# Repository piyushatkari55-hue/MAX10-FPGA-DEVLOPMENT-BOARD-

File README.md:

# MAX 10 FPGA Development Board

## Project Overview
This project focuses on designing a custom FPGA development board based on the **Intel MAX 10 10M02SC E144 (C7G)** FPGA using KiCad EDA.

The aim is to develop a compact, low-cost and beginner-friendly FPGA development platform for learning, testing, and implementing digital logic applications.

## Main Objectives
- Design a complete FPGA schematic and PCB layout.
- Implement suitable power management for the FPGA and peripherals.
- Provide a JTAG interface for FPGA programming and debugging.
- Design clock and FPGA configuration circuits.
- Expose FPGA GPIO pins through expansion headers.
- Develop a compact PCB while following FPGA layout guidelines.

## Hardware Features
- **FPGA:** Intel MAX 10 10M02SC E144
- **EDA Tool:** KiCad
- **Programming Interface:** JTAG
- **Clock Circuit:** External clock source
- **Power Management:** Voltage regulation and decoupling
- **Expansion:** GPIO headers for external peripherals

## Repository Structure
- `10M02SCE144C7G.kicad_pro` – KiCad project file
- `10M02SCE144C7G.kicad_sch` – Circuit schematic
- `10M02SCE144C7G.kicad_pcb` – PCB layout

## Project Status
Currently in development. Schematic design and PCB development are ongoing.

## Future Scope
- Complete PCB routing and design verification.
- Fabricate and assemble the PCB.
- Test FPGA programming and GPIO functionality.
- Validate power supplies and clock operation.

## Tools & Technologies
- KiCad EDA
- Intel MAX 10 FPGA
- PCB Design
- Digital Electronics
- Hardware Development

---

**Designed as an academic electronics engineering project.**

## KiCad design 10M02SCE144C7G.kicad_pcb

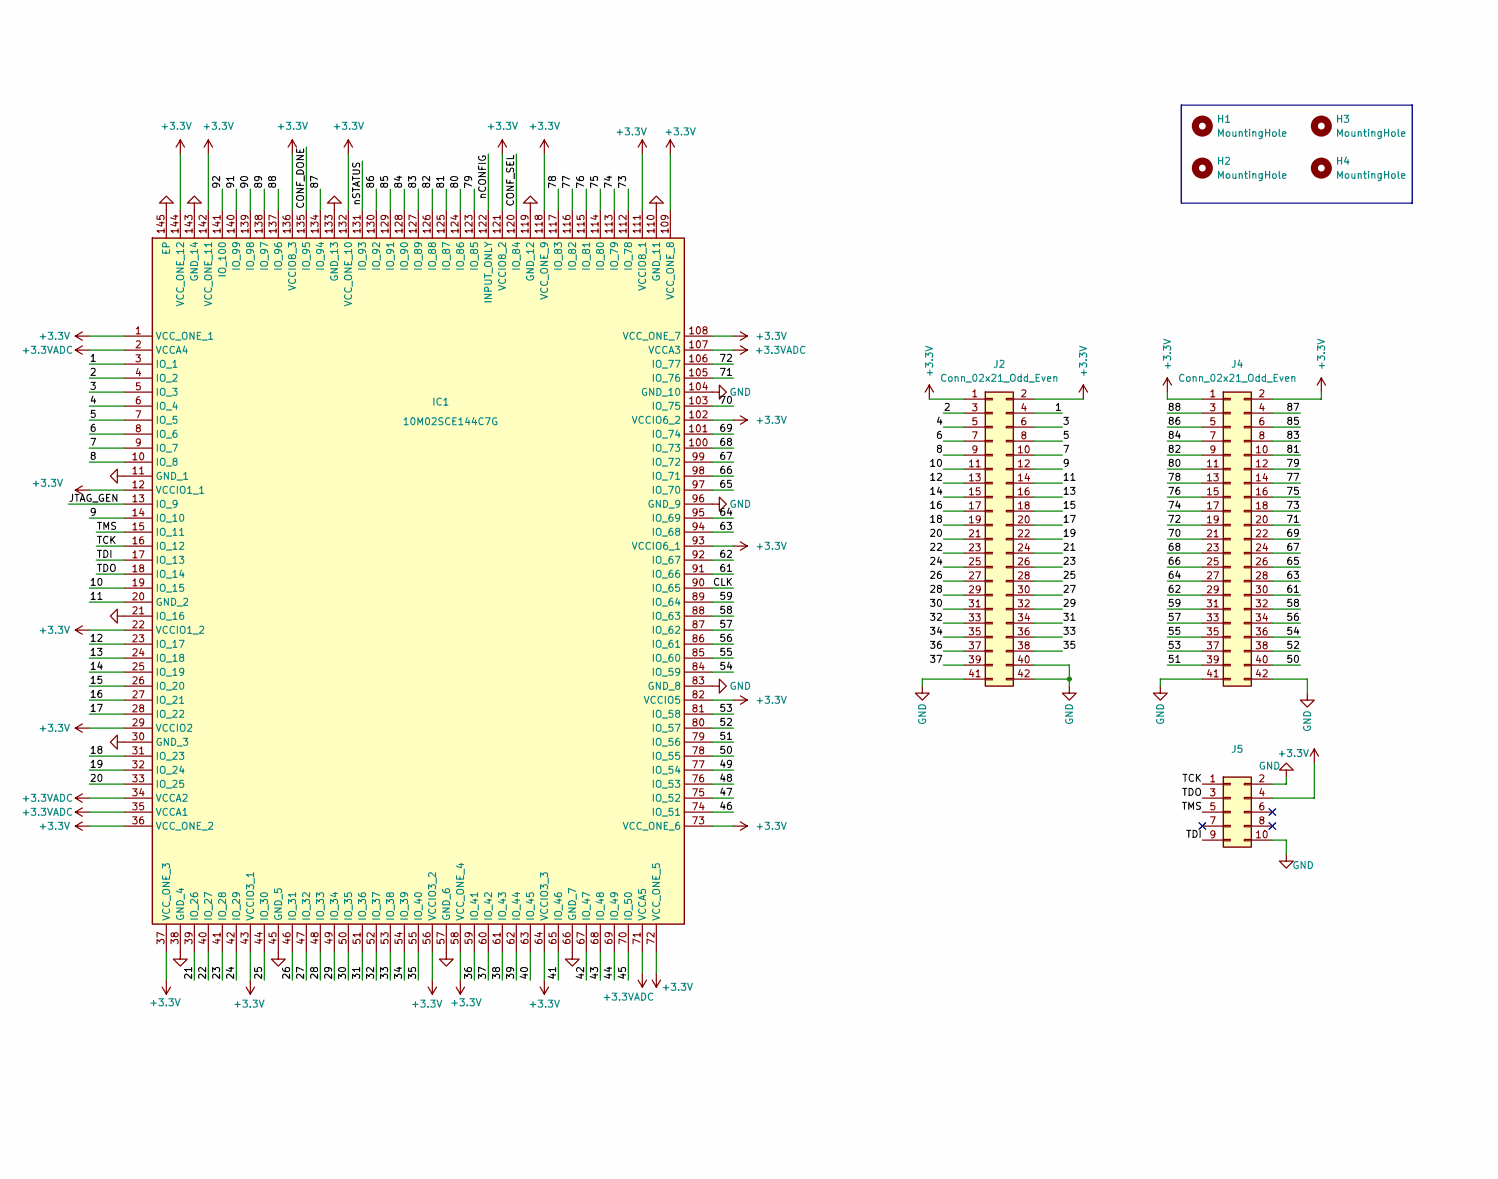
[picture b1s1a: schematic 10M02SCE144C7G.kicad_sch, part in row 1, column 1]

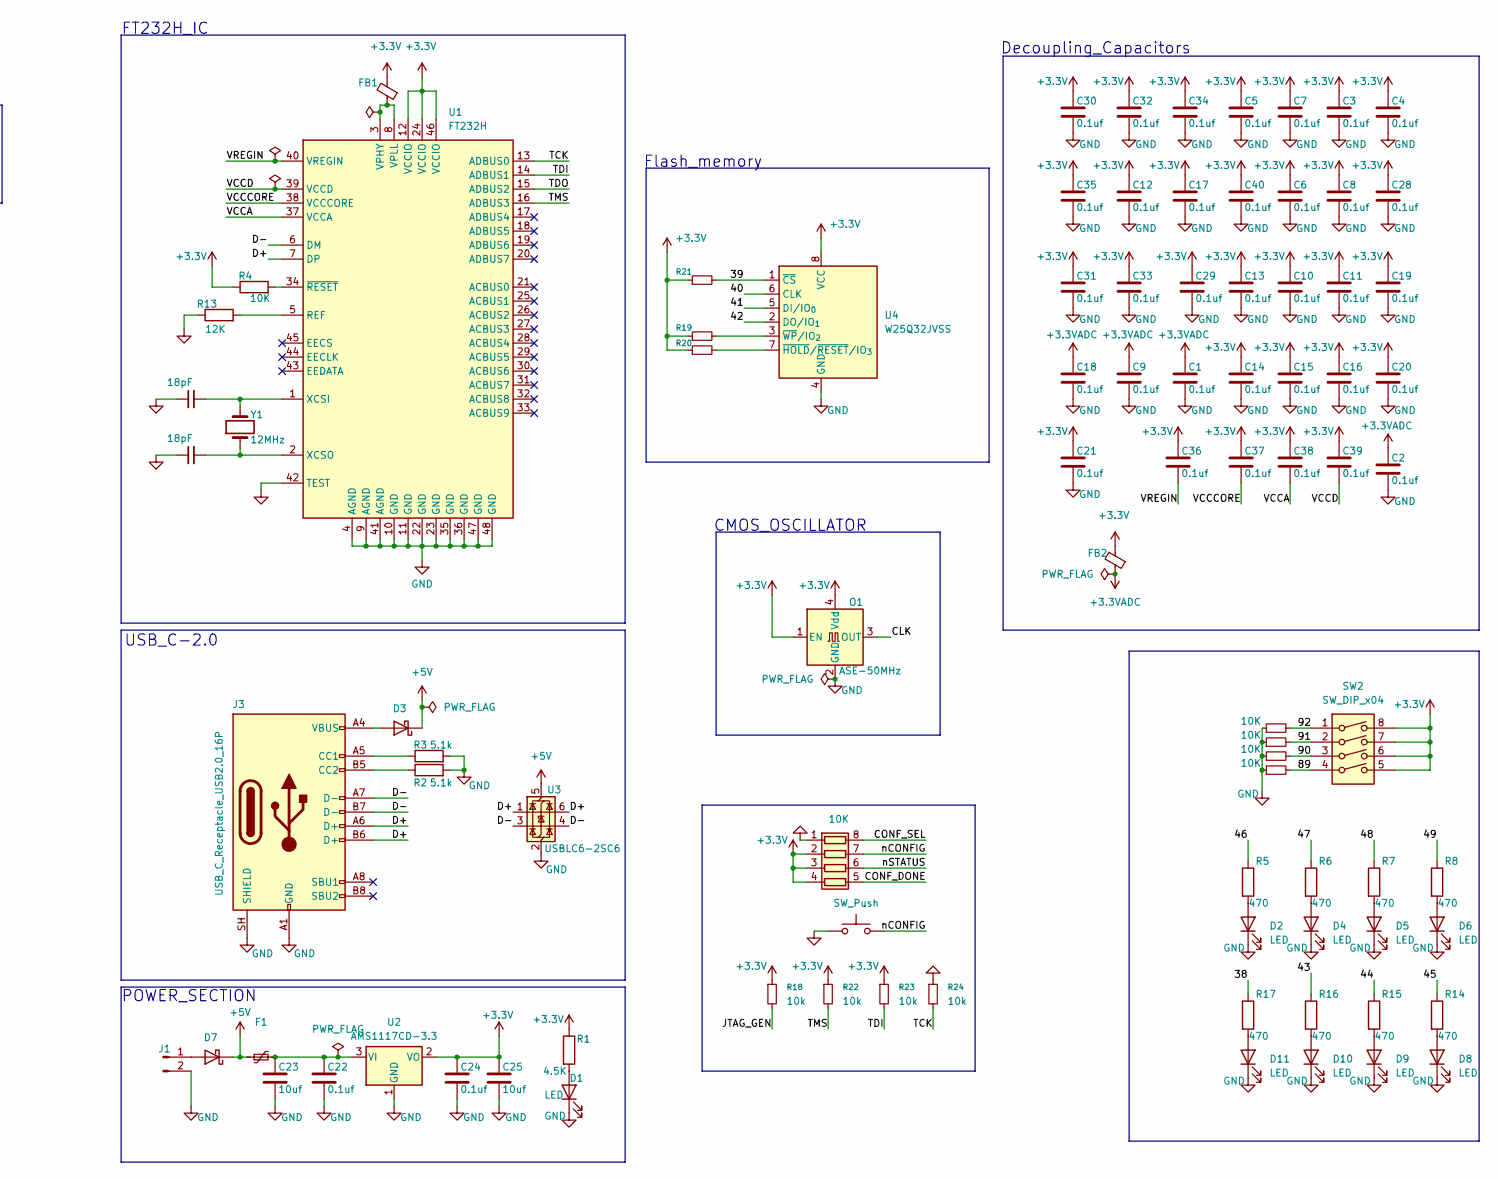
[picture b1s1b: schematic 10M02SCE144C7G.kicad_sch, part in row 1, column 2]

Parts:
C1, C2, C3, C4, C5, C6, C7, C8, C9, C10, C11, C12, C13, C14, C15, C16, C17, C18, C19, C20, C21, C22, C24, C28, C29, C30, C31, C32, C33, C34, C35, C40: 0.1uf; C_0402_1005Metric
C23, C25: 10uf; C_0805_2012Metric
C26, C27: 18pF; C_0603_1608Metric
C36, C37, C38, C39: 0.1uf; C_0603_1608Metric
D1, D2, D4, D5, D6, D8, D9, D10, D11: LED; LED_0603_1608Metric
D3, D7: D_Schottky; D_SOD-323
F1: Polyfuse_Small; Fuse_1206_3216Metric
FB1: FerriteBead_Small; L_0603_1608Metric
FB2: FerriteBead_Small; L_0402_1005Metric
H1, H2, H3, H4: MountingHole; MountingHole_2.7mm_M2.5_Pad_Via
IC1: 10M02SCE144C7G; 10M02SCE144; Manufacturer_Part_Number 10M02SCE144A7G; Mouser Part Number 989-10M02SCE144A7G
J1: Conn_01x02_Pin; JST_EH_B2B-EH-A_1x02_P2.50mm_Vertical
J2, J4: Conn_02x21_Odd_Even; PinHeader_2x21_P2.54mm_Vertical
J3: USB_C_Receptacle_USB2.0_16P; USB_C_Receptacle_GCT_USB4105-xx-A_16P_TopMnt_Horizontal
J5: Conn_02x05_Odd_Even; PinHeader_2x05_P2.54mm_Vertical
O1: ASE-50MHz; Oscillator_SMD_Abracon_ASE-4Pin_3.2x2.5mm
R1: 4.5K; R_0603_1608Metric
R2, R3: 5.1k; R_0603_1608Metric
R4, R9, R10, R11, R12: 10K; R_0603_1608Metric
R5, R6, R7, R8, R14, R15, R16, R17: 470; R_0603_1608Metric
R13: 12K; R_0603_1608Metric
R18, R19, R20, R21, R22, R23, R24: 10k; R_0603_1608Metric
RN2: 10K; R_Array_Convex_4x0603
SW1: SW_Push; SW_Push_SPST_NO_Alps_SKRK
SW2: SW_DIP_x04; SW_DIP_SPSTx04_Slide_9.78x12.34mm_W8.61mm_P2.54mm
U1: FT232H; QFN-48-1EP_8x8mm_P0.5mm_EP6.2x6.2mm_ThermalVias
U2: AMS1117CD-3.3; TO-252-3_TabPin2
U3: USBLC6-2SC6; SOT-23-6
U4: W25Q32JVSS; SOIC-8_5.3x5.3mm_P1.27mm
Y1: 12MHz; R_0603_1608Metric

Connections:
+3.3V: C3.1, C4.1, C5.1, C6.1, C7.1, C8.1, C10.1, C11.1, C12.1, C13.1, C14.1, C15.1, C16.1, C17.1, C19.1, C20.1, C21.1, C24.1, C25.1, C28.1, C29.1, C30.1, C31.1, C32.1, C33.1, C34.1, C35.1, C36.1, C37.1, C38.1, C39.1, C40.1, FB1.2, FB2.2, IC1.1 (VCC_ONE_1), IC1.12 (VCCIO1_1), IC1.22 (VCCIO1_2), IC1.29 (VCCIO2), IC1.36 (VCC_ONE_2), IC1.37 (VCC_ONE_3), IC1.43 (VCCIO3_1), IC1.56 (VCCIO3_2), IC1.58 (VCC_ONE_4), IC1.64 (VCCIO3_3), IC1.72 (VCC_ONE_5), IC1.73 (VCC_ONE_6), IC1.82 (VCCIO5), IC1.93 (VCCIO6_1), IC1.102 (VCCIO6_2), IC1.108 (VCC_ONE_7), IC1.109 (VCC_ONE_8), IC1.111 (VCCIO8_1), IC1.118 (VCC_ONE_9), IC1.121 (VCCIO8_2), IC1.132 (VCC_ONE_10), IC1.136 (VCCIO8_3), IC1.142 (VCC_ONE_11), IC1.144 (VCC_ONE_12), J2.1, J2.2, J4.1, J4.2, J5.4, O1.1 (EN), O1.4 (Vdd), R1.1, R4.1, R18.1, R19.1, R20.1, R21.1, R22.1, R23.1, RN2.2 (R2.1), RN2.3 (R3.1), RN2.4 (R4.1), SW2.5, SW2.6, SW2.7, SW2.8, U1.12 (VCCIO), U1.24 (VCCIO), U1.46 (VCCIO), U2.2 (VO), U4.8 (VCC)
+3.3VADC: C1.1, C2.1, C9.1, C18.1, FB2.1, IC1.2 (VCCA4), IC1.34 (VCCA2), IC1.35 (VCCA1), IC1.71 (VCCA5), IC1.107 (VCCA3)
+5V: D3.1 (K), D7.1 (K), F1.1, U3.5 (VBUS)
/1: IC1.3 (IO_1), J2.4
/2: IC1.4 (IO_2), J2.3
/3: IC1.5 (IO_3), J2.6
/4: IC1.6 (IO_4), J2.5
/5: IC1.7 (IO_5), J2.8
/6: IC1.8 (IO_6), J2.7
/7: IC1.9 (IO_7), J2.10
/8: IC1.10 (IO_8), J2.9
/9: IC1.14 (IO_10), J2.12
/10: IC1.19 (IO_15), J2.11
/11: IC1.20 (GND_2), J2.14
/12: IC1.23 (IO_17), J2.13
/13: IC1.24 (IO_18), J2.16
/14: IC1.25 (IO_19), J2.15
/15: IC1.26 (IO_20), J2.18
/16: IC1.27 (IO_21), J2.17
/17: IC1.28 (IO_22), J2.20
/18: IC1.31 (IO_23), J2.19
/19: IC1.32 (IO_24), J2.22
/20: IC1.33 (IO_25), J2.21
/21: IC1.39 (IO_26), J2.24
/22: IC1.40 (IO_27), J2.23
/23: IC1.41 (IO_28), J2.26
/24: IC1.42 (IO_29), J2.25
/25: IC1.44 (IO_30), J2.28
/26: IC1.46 (IO_31), J2.27
/27: IC1.47 (IO_32), J2.30
/28: IC1.48 (IO_33), J2.29
/29: IC1.49 (IO_34), J2.32
/30: IC1.50 (IO_35), J2.31
/31: IC1.51 (IO_36), J2.34
/32: IC1.52 (IO_37), J2.33
/33: IC1.53 (IO_38), J2.36
/34: IC1.54 (IO_39), J2.35
/35: IC1.55 (IO_40), J2.38
/36: IC1.59 (IO_41), J2.37
/37: IC1.60 (IO_42), J2.39
/38: IC1.61 (IO_43), R17.1
/39: IC1.62 (IO_44), R21.2, U4.1 (~CS)
/40: IC1.63 (IO_45), U4.6 (CLK)
/41: IC1.65 (IO_46), U4.5 (DI/IO_{0})
/42: IC1.67 (IO_47), U4.2 (DO/IO_{1})
/43: IC1.68 (IO_48), R16.1
/44: IC1.69 (IO_49), R15.1
/45: IC1.70 (IO_50), R14.1
/46: IC1.74 (IO_51), R5.1
/47: IC1.75 (IO_52), R6.1
/48: IC1.76 (IO_53), R7.1
/49: IC1.77 (IO_54), R8.1
/50: IC1.78 (IO_55), J4.40
/51: IC1.79 (IO_56), J4.39
/52: IC1.80 (IO_57), J4.38
/53: IC1.81 (IO_58), J4.37
/54: IC1.84 (IO_59), J4.36
/55: IC1.85 (IO_60), J4.35
/56: IC1.86 (IO_61), J4.34
/57: IC1.87 (IO_62), J4.33
/58: IC1.88 (IO_63), J4.32
/59: IC1.89 (IO_64), J4.31
/61: IC1.91 (IO_66), J4.30
/62: IC1.92 (IO_67), J4.29
/63: IC1.94 (IO_68), J4.28
/64: IC1.95 (IO_69), J4.27
/65: IC1.97 (IO_70), J4.26
/66: IC1.98 (IO_71), J4.25
/67: IC1.99 (IO_72), J4.24
/68: IC1.100 (IO_73), J4.23
/69: IC1.101 (IO_74), J4.22
/70: IC1.103 (IO_75), J4.21
/71: IC1.105 (IO_76), J4.20
/72: IC1.106 (IO_77), J4.19
/73: IC1.112 (IO_78), J4.18
/74: IC1.113 (IO_79), J4.17
/75: IC1.114 (IO_80), J4.16
/76: IC1.115 (IO_81), J4.15
/77: IC1.116 (IO_82), J4.14
/78: IC1.117 (IO_83), J4.13
/79: IC1.123 (IO_85), J4.12
/80: IC1.124 (IO_86), J4.11
/81: IC1.125 (IO_87), J4.10
/82: IC1.126 (IO_88), J4.9
/83: IC1.127 (IO_89), J4.8
/84: IC1.128 (IO_90), J4.7
/85: IC1.129 (IO_91), J4.6
/86: IC1.130 (IO_92), J4.5
/87: IC1.134 (IO_94), J4.4
/88: IC1.137 (IO_96), J4.3
/89: IC1.138 (IO_97), R12.2, SW2.4
/90: IC1.139 (IO_98), R11.2, SW2.3
/91: IC1.140 (IO_99), R10.2, SW2.2
/92: IC1.141 (IO_100), R9.2, SW2.1
/CLK: IC1.90 (IO_65), O1.3 (OUT)
/CONF_DONE: IC1.135 (IO_95), RN2.5 (R4.2)
/CONF_SEL: IC1.120 (IO_84), RN2.8 (R1.2)
/D+: J3.A6 (D+), J3.B6 (D+), U1.7 (DP), U3.1 (I/O1), U3.6 (I/O1)
/D-: J3.A7 (D-), J3.B7 (D-), U1.6 (DM), U3.3 (I/O2), U3.4 (I/O2)
/JTAG_GEN: IC1.13 (IO_9), R18.2
/TCK: IC1.16 (IO_12), J5.1, R24.2, U1.13 (ADBUS0)
/TDI: IC1.17 (IO_13), J5.9, R23.2, U1.14 (ADBUS1)
/TDO: IC1.18 (IO_14), J5.3, U1.15 (ADBUS2)
/TMS: IC1.15 (IO_11), J5.5, R22.2, U1.16 (ADBUS3)
/VCCA: C38.2, U1.37 (VCCA)
/VCCCORE: C37.2, U1.38 (VCCCORE)
/VCCD: C39.2, U1.39 (VCCD)
/VREGIN: C36.2, U1.40 (VREGIN)
/nCONFIG: IC1.122 (INPUT_ONLY), RN2.7 (R2.2), SW1.2
/nSTATUS: IC1.131 (IO_93), RN2.6 (R3.2)
GND: C1.2, C2.2, C3.2, C4.2, C5.2, C6.2, C7.2, C8.2, C9.2, C10.2, C11.2, C12.2, C13.2, C14.2, C15.2, C16.2, C17.2, C18.2, C19.2, C20.2, C21.2, C22.2, C23.2, C24.2, C25.2, C26.1, C27.1, C28.2, C29.2, C30.2, C31.2, C32.2, C33.2, C34.2, C35.2, C40.2, D1.1 (K), D2.1 (K), D4.1 (K), D5.1 (K), D6.1 (K), D8.1 (K), D9.1 (K), D10.1 (K), D11.1 (K), IC1.11 (GND_1), IC1.21 (IO_16), IC1.30 (GND_3), IC1.38 (GND_4), IC1.45 (GND_5), IC1.57 (GND_6), IC1.66 (GND_7), IC1.83 (GND_8), IC1.96 (GND_9), IC1.104 (GND_10), IC1.110 (GND_11), IC1.119 (GND_12), IC1.133 (GND_13), IC1.143 (GND_14), IC1.145 (EP), J1.2, J2.40, J2.41, J2.42, J3.A1 (GND), J3.A12 (GND), J3.B1 (GND), J3.B12 (GND), J3.SH (SHIELD), J4.41, J4.42, J5.2, J5.10, O1.2 (GND), R2.2, R3.2, R9.1, R10.1, R11.1, R12.1, R13.1, R24.1, RN2.1 (R1.1), SW1.1, U1.4 (AGND), U1.9 (AGND), U1.10 (GND), U1.11 (GND), U1.22 (GND), U1.23 (GND), U1.35 (GND), U1.36 (GND), U1.41 (AGND), U1.42 (TEST), U1.47 (GND), U1.48 (GND), U2.1 (GND), U3.2 (GND), U4.4 (GND)
unnamed: D1.2 (A), R1.2
unnamed: D2.2 (A), R5.2
unnamed: D3.2 (A), J3.A4 (VBUS), J3.A9 (VBUS), J3.B4 (VBUS), J3.B9 (VBUS)
unnamed: D4.2 (A), R6.2
unnamed: D5.2 (A), R7.2
unnamed: D6.2 (A), R8.2
unnamed: D7.2 (A), J1.1
unnamed: D8.2 (A), R14.2
unnamed: D9.2 (A), R15.2
unnamed: D10.2 (A), R16.2
unnamed: D11.2 (A), R17.2
unnamed: J3.A5 (CC1), R3.1
unnamed: J3.B5 (CC2), R2.1
unnamed: R13.2, U1.5 (REF)
unnamed: FB1.1, U1.3 (VPHY), U1.8 (VPLL)
unnamed: C26.2, U1.1 (XCSI), Y1.2
unnamed: C27.2, U1.2 (XCSO), Y1.1
unnamed: R4.2, U1.34 (~RESET)
unnamed: C22.1, C23.1, F1.2, U2.3 (VI)
unnamed: R20.2, U4.7 (~HOLD/~RESET/IO_{3})
unnamed: R19.2, U4.3 (~WP/IO_{2})

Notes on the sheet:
FT232H_IC
CMOS_OSCILLATOR
USB_C-2.0
POWER_SECTION
Flash_memory
Decoupling_Capacitors

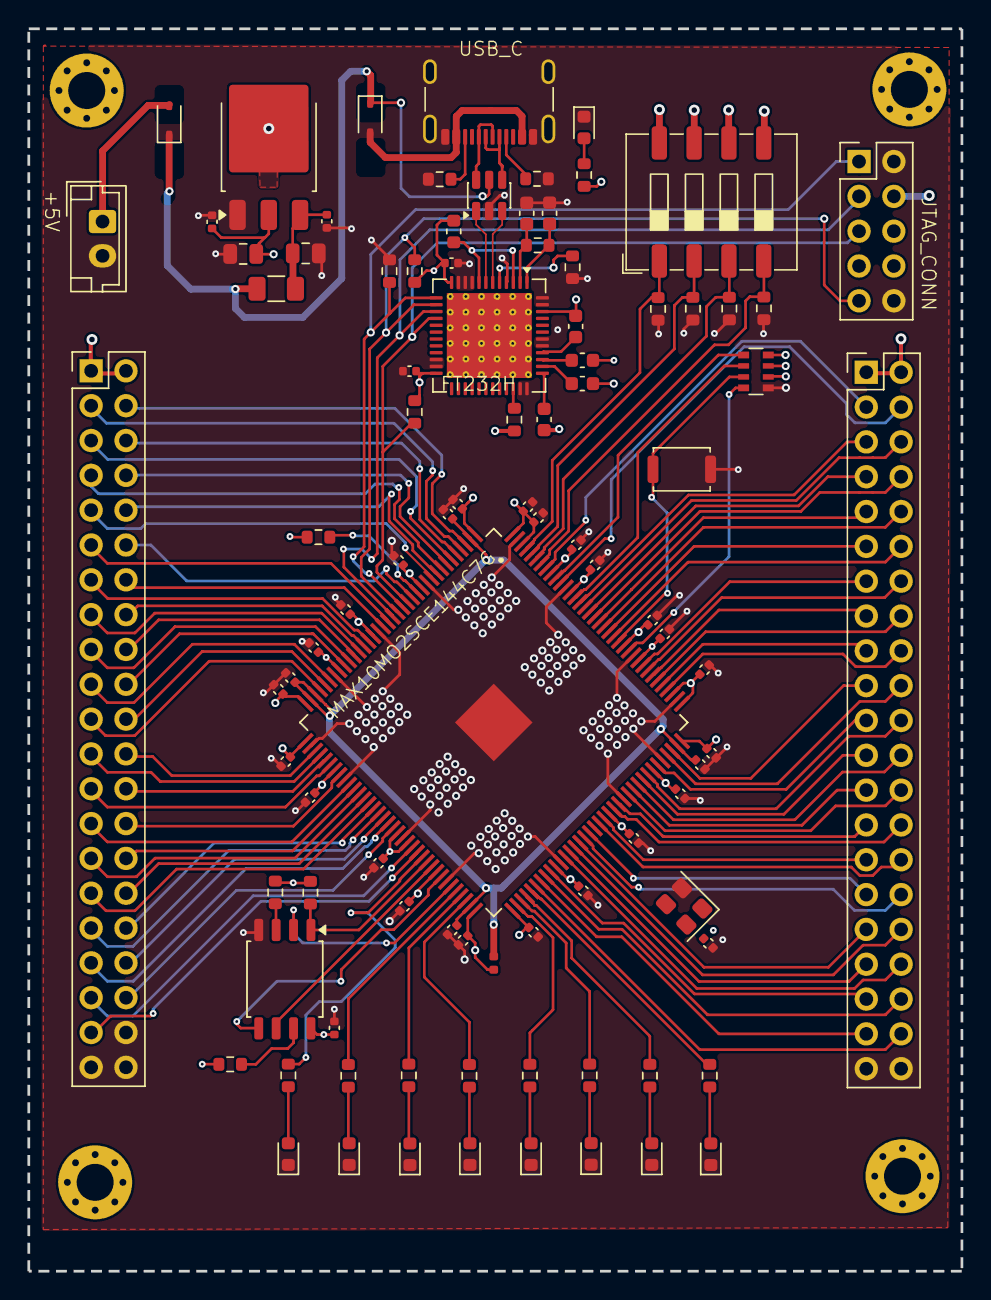
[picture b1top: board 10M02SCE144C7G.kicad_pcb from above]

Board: 4 copper layers, 68.1 x 90.6 mm, 97 parts (0 on the bottom side), 132 nets.
